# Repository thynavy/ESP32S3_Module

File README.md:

# Project Title: **ESP32_S3 Module**

This repository contains the PCB design files for a custom ESP32-S3 module created using KiCad. The ESP32-S3, developed by Espressif Systems, is a powerful microcontroller with Wi-Fi and Bluetooth Low Energy (BLE) capabilities, making it ideal for IoT applications, edge computing, and AI-based solutions. This module design aims to provide a compact and flexible solution for integrating the ESP32-S3 into various embedded projects.
<p align="center">
    
    <br />
    <strong>Figure 1: The ESP32-S3 Module</strong>
</p>

#  Project Features

- **Wi-Fi and BLE Connectivity**: Supports dual-core processing and efficient communication via Wi-Fi and BLE.
- **Modular Design**: Designed for easy integration into existing systems or as a standalone controller.
- **Optimized PCB Layout**: Careful component placement and trace routing for efficient power management and signal integrity.
- **Flexible I/O**: Provides a variety of GPIO pins for connecting sensors, actuators, and other peripherals.

##  About the Design

This design was created in KiCad and includes both schematic and PCB layout files. The module is intended for applications requiring reliable wireless communication and processing power, suitable for IoT devices, sensor networks, and general-purpose automation projects.

Feel free to clone this repository, explore the design files, and adapt the module for your own projects. Contributions and feedback are welcome!

##  Documentation

For more detailed information on the ESP32-S3 module design, you can view the full documentation here:

[ESP32-S3 Module Schematic (PDF)](https://github.com/thynavy/ESP32S3_Module/blob/main/19.%20ESP32%20Module.pdf)

[ESP32-S3 Module Design Documentation (PDF)](https://github.com/thynavy/ESP32S3_Module/blob/main/esp32-s3-wroom-1_wroom-1u_datasheet_en.pdf)

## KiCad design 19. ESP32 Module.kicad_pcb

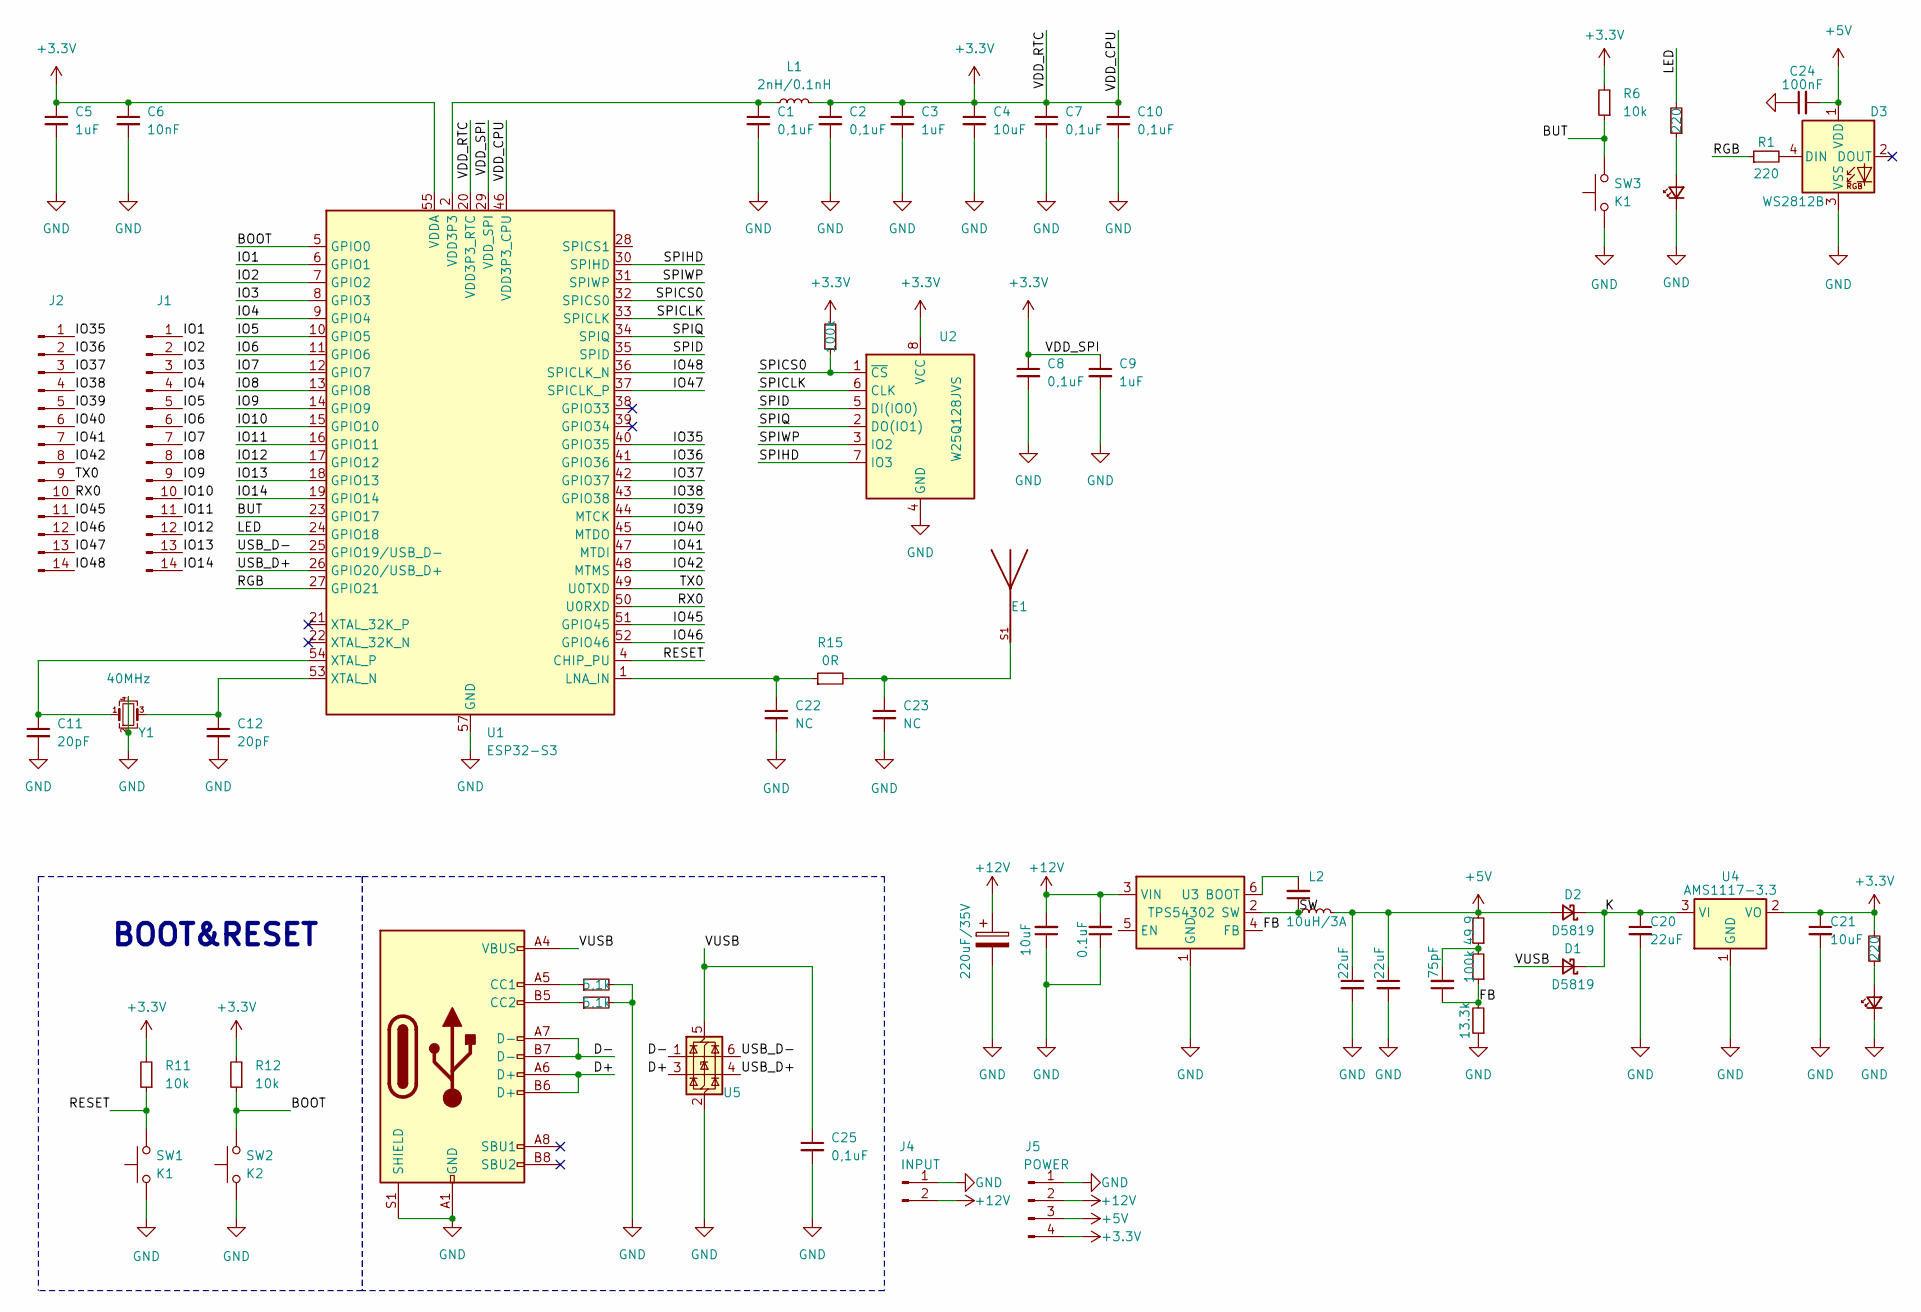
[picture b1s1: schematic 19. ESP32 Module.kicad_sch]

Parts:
C1, C2, C7, C8, C10, C25: 0,1uF; C_0603_1608Metric
C3, C5, C9: 1uF; C_0603_1608Metric
C4, C14: 10uF; C_0603_1608Metric
C6: 10nF; C_0603_1608Metric
C11, C12: 20pF; C_0603_1608Metric
C13: 220uF/35V; CP_Elec_6.3x7.7
C15: 0.1uF; C_0603_1608Metric
C16: 100n; C_0603_1608Metric
C17, C18: 22uF; C_0603_1608Metric
C19: 75pF; C_0603_1608Metric
C20: 22uF; C_0805_2012Metric
C21: 10uF; C_0805_2012Metric
C22, C23: NC; C_0603_1608Metric
C24: 100nF; C_0603_1608Metric
D1, D2: D5819; D_SOD-123
D3: WS2812B; LED_WS2812B_PLCC4_5.0x5.0mm_P3.2mm
D4, D5: LED_PWR; LED_0603_1608Metric
E1: ANT5320LL45R2400A; XCVR_ANT5320LL45R2400A; PARTREV Version 1
J1, J2: Conn_01x14_Pin; PinHeader_1x14_P2.54mm_Vertical
J3: USB_C_Receptacle_USB2.0_16P; USB_C_Receptacle_Palconn_UTC16-G
J4: INPUT; PinHeader_1x02_P2.54mm_Vertical
J5: POWER; PinHeader_1x04_P2.54mm_Vertical
L1: 2nH/0.1nH; L_0603_1608Metric
L2: 10uH/3A; L_Abracon_ASPI-0630LR
R1, R2, R3: 220; R_0603_1608Metric
R4, R5: 5,1k; R_0603_1608Metric
R6, R11, R12: 10k; R_0603_1608Metric
R7: 49.9; R_0603_1608Metric
R8, R10: 100k; R_0603_1608Metric
R9: 13.3k; R_0603_1608Metric
R15: 0R; R_0603_1608Metric
SW1, SW3: K1; SW_Push_1P1T_NO_Vertical_Wuerth_434133025816
SW2: K2; SW_Push_1P1T_NO_Vertical_Wuerth_434133025816
U1: ESP32-S3; QFN-56-1EP_7x7mm_P0.4mm_EP4x4mm
U2: W25Q128JVS; SOIC-8_5.23x5.23mm_P1.27mm
U3: TPS54302; SOT-23-6
U4: AMS1117-3.3; SOT-223-3_TabPin2
U5: USBLC6-2SC6; SOT-23-6
Y1: 40MHz; Crystal_SMD_3225-4Pin_3.2x2.5mm

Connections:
+3.3V: C2.1, C3.1, C4.1, C5.1, C6.1, C7.1, C8.1, C9.1, C10.1, C21.1, J5.4, L1.2, R2.2, R6.2, R10.2, R11.2, R12.2, U1.20 (VDD3P3_RTC), U1.29 (VDD_SPI), U1.46 (VDD3P3_CPU), U1.55 (VDDA), U1.56 (VDDA), U2.8 (VCC), U4.2 (VO)
+5V: C17.1, C18.1, C24.2, D2.2 (A), D3.1 (VDD), J5.3, L2.2, R7.2
+12V: C13.1, C14.2, C15.2, J4.2, J5.2, U3.3 (VIN)
/BOOT: R12.1, SW2.2, U1.5 (GPIO0)
/BUT: R6.1, SW3.2, U1.23 (GPIO17)
/D+: J3.A6 (D+), J3.B6 (D+), U5.3 (I/O2)
/D-: J3.A7 (D-), J3.B7 (D-), U5.1 (I/O1)
/FB: C19.1, R8.1, R9.2, U3.4 (FB)
/IO1: J1.1, U1.6 (GPIO1)
/IO2: J1.2, U1.7 (GPIO2)
/IO3: J1.3, U1.8 (GPIO3)
/IO4: J1.4, U1.9 (GPIO4)
/IO5: J1.5, U1.10 (GPIO5)
/IO6: J1.6, U1.11 (GPIO6)
/IO7: J1.7, U1.12 (GPIO7)
/IO8: J1.8, U1.13 (GPIO8)
/IO9: J1.9, U1.14 (GPIO9)
/IO10: J1.10, U1.15 (GPIO10)
/IO11: J1.11, U1.16 (GPIO11)
/IO12: J1.12, U1.17 (GPIO12)
/IO13: J1.13, U1.18 (GPIO13)
/IO14: J1.14, U1.19 (GPIO14)
/IO35: J2.1, U1.40 (GPIO35)
/IO36: J2.2, U1.41 (GPIO36)
/IO37: J2.3, U1.42 (GPIO37)
/IO38: J2.4, U1.43 (GPIO38)
/IO39: J2.5, U1.44 (MTCK)
/IO40: J2.6, U1.45 (MTDO)
/IO41: J2.7, U1.47 (MTDI)
/IO42: J2.8, U1.48 (MTMS)
/IO45: J2.11, U1.51 (GPIO45)
/IO46: J2.12, U1.52 (GPIO46)
/IO47: J2.13, U1.37 (SPICLK_P)
/IO48: J2.14, U1.36 (SPICLK_N)
/K: C20.1, D1.1 (K), D2.1 (K), U4.3 (VI)
/LED: R3.2, U1.24 (GPIO18)
/RESET: R11.1, SW1.2, U1.4 (CHIP_PU)
/RGB: R1.1, U1.27 (GPIO21)
/RX0: J2.10, U1.50 (U0RXD)
/SPICLK: U1.33 (SPICLK), U2.6 (CLK)
/SPICS0: R10.1, U1.32 (SPICS0), U2.1 (~CS)
/SPID: U1.35 (SPID), U2.5 (DI(IO0))
/SPIHD: U1.30 (SPIHD), U2.7 (IO3)
/SPIQ: U1.34 (SPIQ), U2.2 (DO(IO1))
/SPIWP: U1.31 (SPIWP), U2.3 (IO2)
/SW: C16.1, L2.1, U3.2 (SW)
/TX0: J2.9, U1.49 (U0TXD)
/USB_D+: U1.26 (GPIO20/USB_D+), U5.4 (I/O2)
/USB_D-: U1.25 (GPIO19/USB_D-), U5.6 (I/O1)
/VUSB: C25.1, D1.2 (A), J3.A4 (VBUS), J3.A9 (VBUS), J3.B4 (VBUS), J3.B9 (VBUS), U5.5 (VBUS)
GND: C1.2, C2.2, C3.2, C4.2, C5.2, C6.2, C7.2, C8.2, C9.2, C10.2, C11.2, C12.2, C13.2, C14.1, C15.1, C17.2, C18.2, C20.2, C21.2, C22.2, C23.2, C24.1, C25.2, D3.3 (VSS), D4.1 (K), D5.1 (K), J3.A1 (GND), J3.A12 (GND), J3.B1 (GND), J3.B12 (GND), J3.S1 (SHIELD), J4.1, J5.1, R4.2, R5.2, R9.1, SW1.1, SW2.1, SW3.1, U1.57 (GND), U2.4 (GND), U3.1 (GND), U4.1 (GND), U5.2 (GND), Y1.2, Y1.4
unnamed: C1.1, L1.1, U1.2 (VDD3P3), U1.3 (VDD3P3)
unnamed: C19.2, R7.1, R8.2
unnamed: C23.1, E1.S1, R15.2
unnamed: D3.4 (DIN), R1.2
unnamed: D4.2 (A), R2.1
unnamed: D5.2 (A), R3.1
unnamed: J3.A5 (CC1), R4.1
unnamed: J3.B5 (CC2), R5.1
unnamed: C22.1, R15.1, U1.1 (LNA_IN)
unnamed: C12.1, U1.53 (XTAL_N), Y1.3
unnamed: C11.1, U1.54 (XTAL_P), Y1.1
unnamed: C16.2, U3.6 (BOOT)

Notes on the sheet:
BOOT&RESET

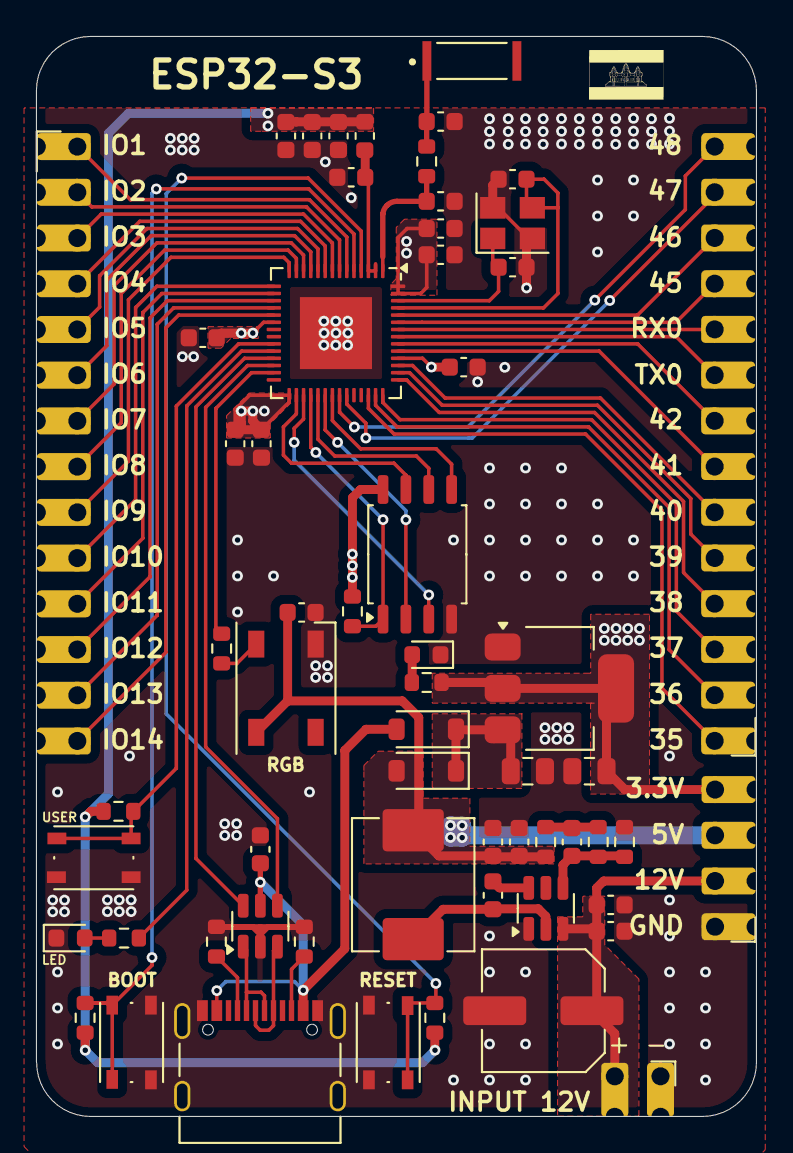
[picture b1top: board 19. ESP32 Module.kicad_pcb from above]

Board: 4 copper layers, 40.0 x 60.0 mm, 60 parts (0 on the bottom side), 63 nets.

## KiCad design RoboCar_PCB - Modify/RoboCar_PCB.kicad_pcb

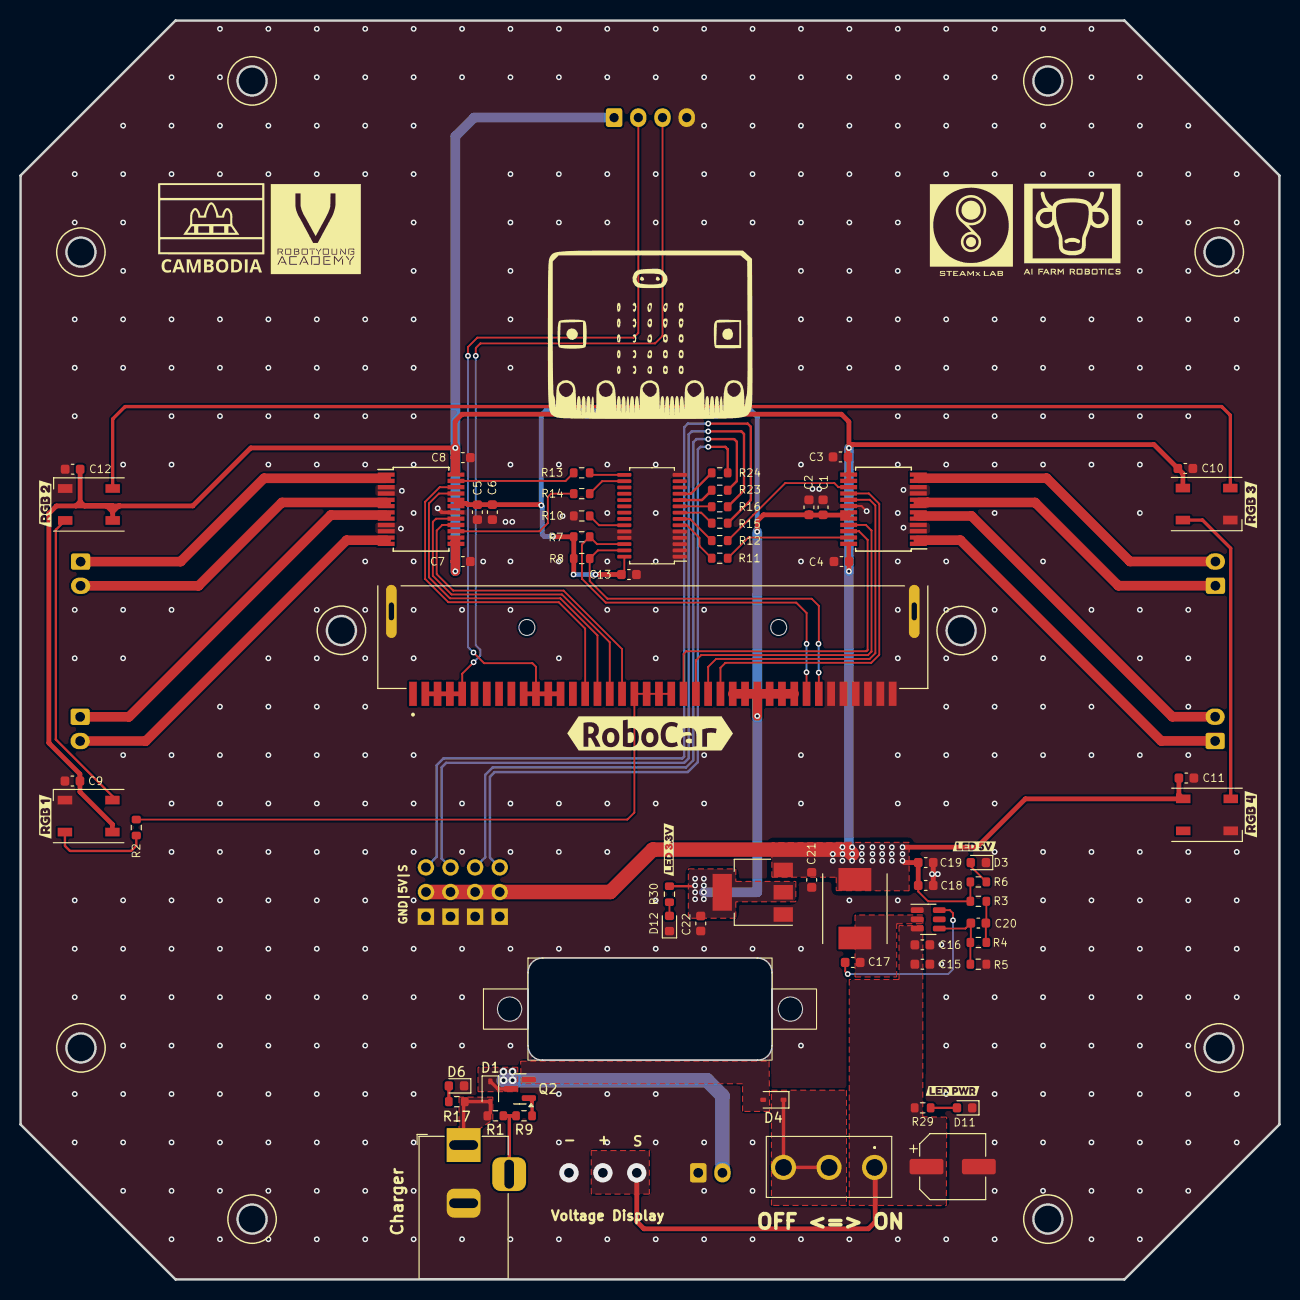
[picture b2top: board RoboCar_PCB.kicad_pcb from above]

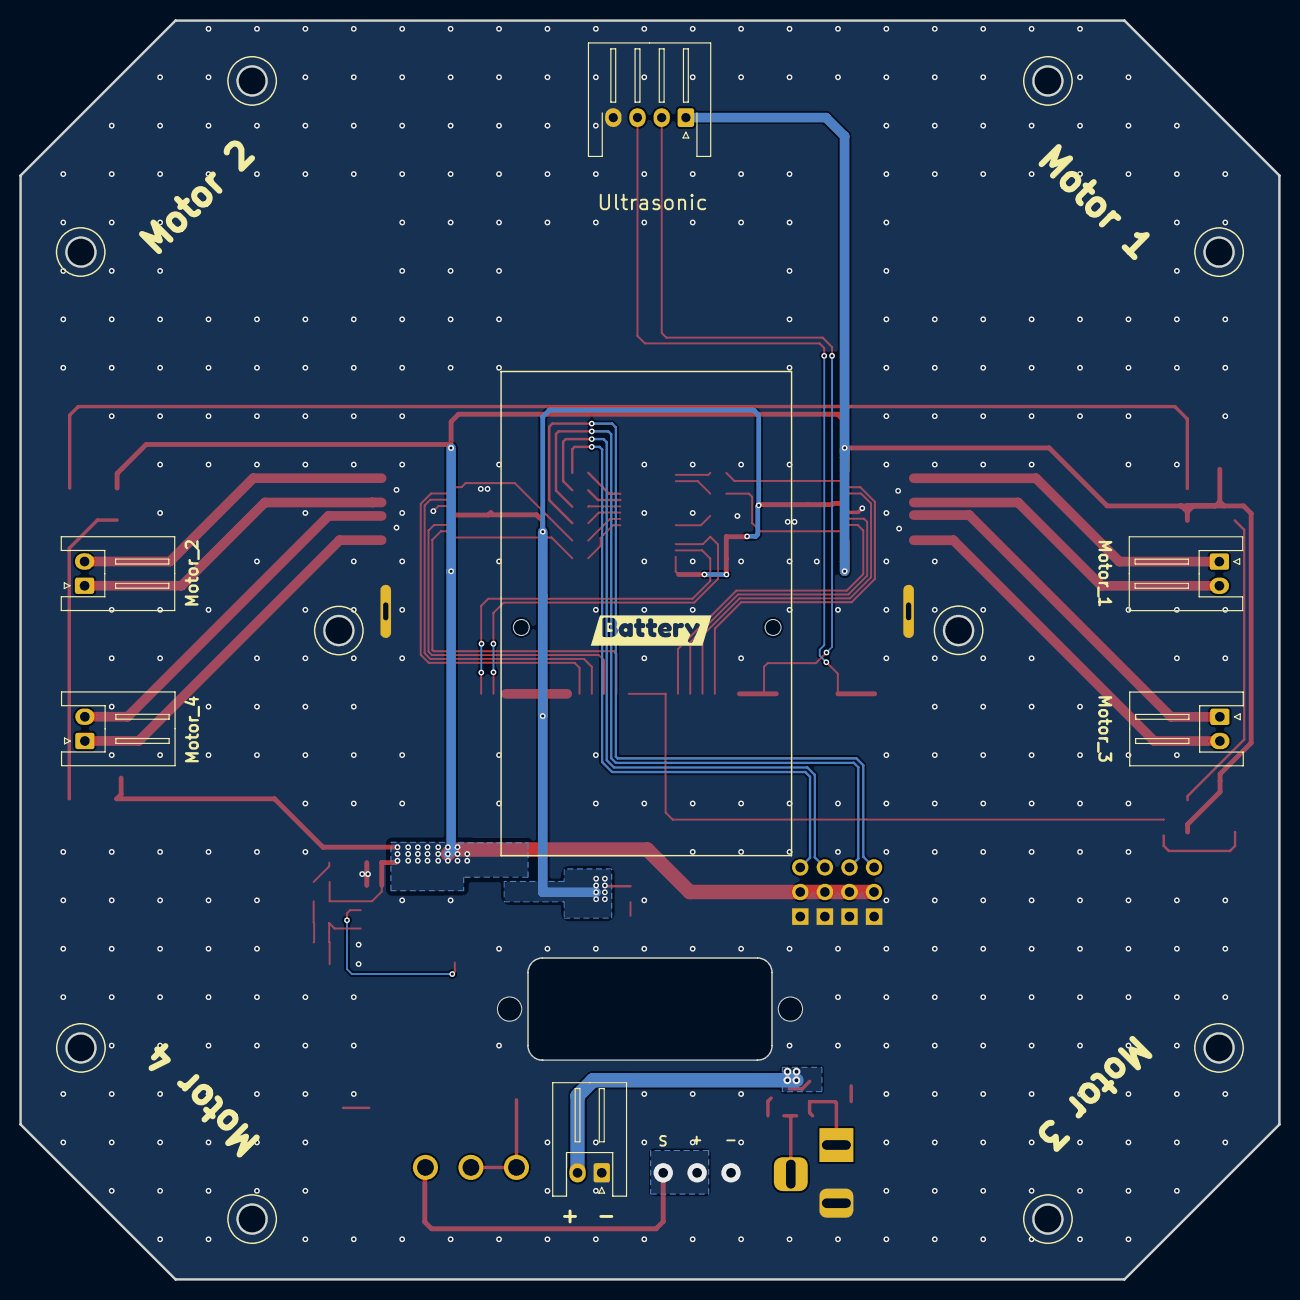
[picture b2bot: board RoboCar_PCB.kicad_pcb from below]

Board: 2 copper layers, 130.0 x 130.0 mm, 81 parts (7 on the bottom side), 60 nets.

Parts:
C1, C4, C5, C8, C15: 10uF; C_0603_1608Metric
C2, C3, C6, C7, C9, C10, C11, C12, C13, C16: 0.1uF; C_0603_1608Metric
C14: 220uF; CP_Elec_6.3x7.7
C17: 100n; C_0603_1608Metric
C18, C19, C21, C22: 22uF; C_0603_1608Metric
C20: 75pF; C_0603_1608Metric
D1, D4: 1N5819WS; D_SOD-323
D2, D5, D8, D9: WS2812B; LED_WS2812B_PLCC4_5.0x5.0mm_P3.2mm
D3, D6, D11, D12: LED_PWR; LED_0603_1608Metric
J1: MIC127-140-001; DONGGUAN_MIC127-140-001
J2: Motor1; JST_XH_S2B-XH-A_1x02_P2.50mm_Horizontal
J3: Motor2; JST_XH_S2B-XH-A_1x02_P2.50mm_Horizontal
J4: Motor3; JST_XH_S2B-XH-A_1x02_P2.50mm_Horizontal
J5: Motor4; JST_XH_S2B-XH-A_1x02_P2.50mm_Horizontal
J6: Battery; JST_XH_S2B-XH-A_1x02_P2.50mm_Horizontal
J7, J8, J9: Conn_01x04_Socket; PinHeader_1x04_P2.54mm_Vertical
J10: Conn_01x04_Socket; JST_XH_S4B-XH-A-1_1x04_P2.50mm_Horizontal
J11: Charger; BarrelJack_Horizontal
L1: 10uH/5A; IND_ASPI0630HI100M
Q2: IRLML6402; SOT-23
R1: 100; R_0603_1608Metric
R2, R11, R12, R13, R14, R15, R16, R23, R24: 220; R_0603_1608Metric
R3: 49.9; R_0603_1608Metric
R4: 100k; R_0603_1608Metric
R5: 13.3k; R_0603_1608Metric
R6, R17, R29, R30: 1k; R_0603_1608Metric
R7, R8, R9, R10: 10k; R_0603_1608Metric
S1: ON/OFF; SPTD_Switch
U1, U2: TB6612FNG; SSOP-24_5.3x8.2mm_P0.65mm
U3: PCA9685PW; TSSOP-28_4.4x9.7mm_P0.65mm
U4: TPS54302; SOT-23-6
U5: AMS1117-3.3; SOT-223-3_TabPin2
kibuzzard-677E35A5: G***; kibuzzard-677E35A5
kibuzzard-67073BE5: G***; kibuzzard-67073BE5
kibuzzard-67073CB6: G***; kibuzzard-67073CB6
kibuzzard-67073D1E: G***; kibuzzard-67073D1E
kibuzzard-67073D02: G***; kibuzzard-67073D02
kibuzzard-6707333C: G***; kibuzzard-6707333C
kibuzzard-6719123F: G***; kibuzzard-6719123F
kibuzzard-6719125B: G***; kibuzzard-6719125B
kibuzzard-67191277: G***; kibuzzard-67191277

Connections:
+3.3V: C1.2, C2.2, C5.2, C6.2, C13.1, C22.1, J1.27 (+3V3_27), J1.28 (+3V3_28), J1.29 (+3V3_29), J1.30 (+3V3_30), J1.31 (+3V3_31), J1.32 (+3V3_32), R7.1, R8.1, R30.2, U1.19 (STBY), U1.20 (VCC), U2.19 (STBY), U2.20 (VCC), U3.28 (VDD), U5.2 (VO)
+5V: C3.2, C4.2, C7.2, C8.2, C9.2, C10.2, C11.2, C12.2, C18.1, C19.1, C21.1, D2.1 (VDD), D5.1 (VDD), D8.1 (VDD), D9.1 (VDD), J9.1, J9.2, J9.3, J9.4, J10.1, L1.2, R3.2, R6.2, U1.13 (VM2), U1.14 (VM3), U1.24 (VM1), U2.13 (VM2), U2.14 (VM3), U2.24 (VM1), U5.3 (VI)
/AM1: J1.24 (P14/SPI1_MISO), U1.21 (AIN1)
/AM2: J1.25 (P15/SPI1_MOSI), U1.17 (BIN1)
/AM3: J1.16 (P10/AIN/LED_COL_3), U2.21 (AIN1)
/AM4: J1.17 (P11/BUTTON_B), U2.17 (BIN1)
/BM1: J1.23 (P13/SPI1_SCK), U1.22 (AIN2)
/BM2: J1.26 (P16), U1.16 (BIN2)
/BM3: J1.15 (P9/LED_COL_7), U2.22 (AIN2)
/BM4: J1.18 (P12/RSVD), U2.16 (BIN2)
/FB: C20.1, R4.1, R5.2, U4.4 (FB)
/M1+: J2.2, U1.5 (AO2), U1.6 (AO2)
/M1-: J2.1, U1.1 (AO1), U1.2 (AO1)
/M2+: J3.1, U1.7 (BO2), U1.8 (BO2)
/M2-: J3.2, U1.11 (BO1), U1.12 (BO1)
/M3+: J4.2, U2.5 (AO2), U2.6 (AO2)
/M3-: J4.1, U2.1 (AO1), U2.2 (AO1)
/M4+: J5.1, U2.7 (BO2), U2.8 (BO2)
/M4-: J5.2, U2.11 (BO1), U2.12 (BO1)
/P0: J1.2 (P0_1/AIN0), J1.3 (P0_2/AIN0), J1.4 (P0_3/AIN0), J1.5 (P0_4/AIN0), J10.3
/P1: J1.10 (P1_1/AIN1), J1.11 (P1_2/AIN1), J1.12 (P1_3/AIN1), J1.13 (P1_4/AIN1), J10.2
/P2: J1.19 (P2_1/AIN2), J1.20 (P2_2/AIN2), J1.21 (P2_3/AIN2), J1.22 (P2_4/AIN2), R2.1
/PWM1: R11.1, U1.23 (PWMA)
/PWM2: R12.1, U1.15 (PWMB)
/PWM3: R13.1, U2.23 (PWMA)
/PWM4: R14.1, U2.15 (PWMB)
/S1: J8.1, R15.1
/S2: J8.2, R16.1
/S3: J8.3, R23.1
/S4: J8.4, R24.1
/SCL: J1.33 (P19/I2C1_SCL), R7.2, U3.26 (SCL)
/SDA: J1.34 (P20/I2C1_SDA), R8.2, U3.27 (SDA)
/SW: C17.1, L1.1, U4.2 (SW)
GND: C1.1, C2.1, C3.1, C4.1, C5.1, C6.1, C7.1, C8.1, C9.1, C10.1, C11.1, C12.1, C13.2, C14.2, C15.1, C16.1, C18.2, C19.2, C21.2, C22.2, D2.3 (VSS), D3.1 (K), D5.3 (VSS), D6.1 (K), D8.3 (VSS), D9.3 (VSS), D11.1 (K), D12.1 (K), J1.35 (GND_35), J1.36 (GND_36), J1.37 (GND_37), J1.38 (GND_38), J1.39 (GND_39), J1.40 (GND_40), J1.S1 (SHIELD), J1.S2 (SHIELD), J6.1, J7.1, J7.2, J7.3, J7.4, J10.4, J11.2, R5.1, R10.1, U1.3 (PGND1), U1.4 (PGND1), U1.9 (PGND2), U1.10 (PGND2), U1.18 (GND), U2.3 (PGND1), U2.4 (PGND1), U2.9 (PGND2), U2.10 (PGND2), U2.18 (GND), U3.1 (A0), U3.2 (A1), U3.3 (A2), U3.4 (A3), U3.5 (A4), U3.14 (VSS), U3.24 (A5), U3.25 (EXTCLK), U4.1 (GND), U5.1 (GND)
NC: D4.1 (K), S1.2 (COM), S1.3 (NC)
unnamed: C20.2, R3.1, R4.2
unnamed: D2.4 (DIN), D5.2 (DOUT)
unnamed: D2.2 (DOUT), D9.4 (DIN)
unnamed: D3.2 (A), R6.1
unnamed: D5.4 (DIN), R2.2
unnamed: D6.2 (A), R17.1
unnamed: D8.4 (DIN), D9.2 (DOUT)
unnamed: D11.2 (A), R29.1
unnamed: D12.2 (A), R30.1
unnamed: J11.3, R1.1, R9.2
unnamed: Q2.1 (G), R9.1
unnamed: R11.2, U3.6 (LED0)
unnamed: R12.2, U3.7 (LED1)
unnamed: R15.2, U3.8 (LED2)
unnamed: R16.2, U3.9 (LED3)
unnamed: R23.2, U3.10 (LED4)
unnamed: R24.2, U3.11 (LED5)
unnamed: R13.2, U3.15 (LED8)
unnamed: R14.2, U3.16 (LED9)
unnamed: R10.2, U3.23 (~OE)
unnamed: C17.2, U4.6 (BOOT)
VIN: D4.2 (A), Q2.2 (S)
V_Bat: D1.1 (K), J6.2, Q2.3 (D)
V_Charger: D1.2 (A), J11.1, R1.2, R17.2
Vs: C14.1, C15.2, C16.2, R29.2, S1.1 (NO), U4.3 (VIN)

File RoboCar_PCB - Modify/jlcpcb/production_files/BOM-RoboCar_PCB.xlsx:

Comment | Designator | Footprint | LCSC | Quantity
TB6612FNG | U1,U2 | SSOP-24_5.3x8.2mm_P0.65mm | C141517 | 2
0.1uF | C10,C11,C12,C13,C16,C17,C2,C3,C6,C7,C9 | C_0603_1608Metric | C14663 | 11
75pF | C20 | C_0603_1608Metric | C1681 | 1
1N5819WS | D1,D4 | D_SOD-323 | C191023 | 2
10uF | C1,C15,C4,C5,C8 | C_0603_1608Metric | C19702 | 5
1k | R17,R29,R30,R6 | R_0603_1608Metric | C21190 | 4
100 | R1 | R_0603_1608Metric | C22775 | 1
LED_PWR | D11,D3,D6 | LED_0603_1608Metric | C2286 | 3
LED_PWR | D12 | LED_0603_1608Metric | C2290 | 1
220 | R11,R12,R13,R14,R15,R16,R2,R23,R24 | R_0603_1608Metric | C22962 | 9
49.9 | R3 | R_0603_1608Metric | C23185 | 1
100k | R4 | R_0603_1608Metric | C25803 | 1
10k | R10,R7,R8,R9 | R_0603_1608Metric | C25804 | 4
IRLML6402 | Q2 | SOT-23 | C2593 | 1
13.3k | R5 | R_0603_1608Metric | C25952 | 1
PCA9685PW | U3 | TSSOP-28_4.4x9.7mm_P0.65mm | C2678753 | 1
WS2812B | D2,D5,D8,D9 | LED_WS2812B_PLCC4_5.0x5.0mm_P3.2mm | C2843785 | 4
TPS54302 | U4 | SOT-23-6 | C311983 | 1
ON/OFF | S1 | SPTD_Switch | C319012 | 1
220uF | C14 | CP_Elec_6.3x7.7 | C3342 | 1
Charger | J11 | BarrelJack_Horizontal | C381116 | 1
22uF | C18,C19,C21,C22 | C_0603_1608Metric | C59461 | 4
AMS1117-3.3 | U5 | SOT-223-3_TabPin2 | C6186 | 1
Conn_01x04_Socket | J7,J8,J9 | PinHeader_1x04_P2.54mm_Vertical | C706876 | 3

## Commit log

2024-11-04 Create KiCad
    all KiCAD files designed
